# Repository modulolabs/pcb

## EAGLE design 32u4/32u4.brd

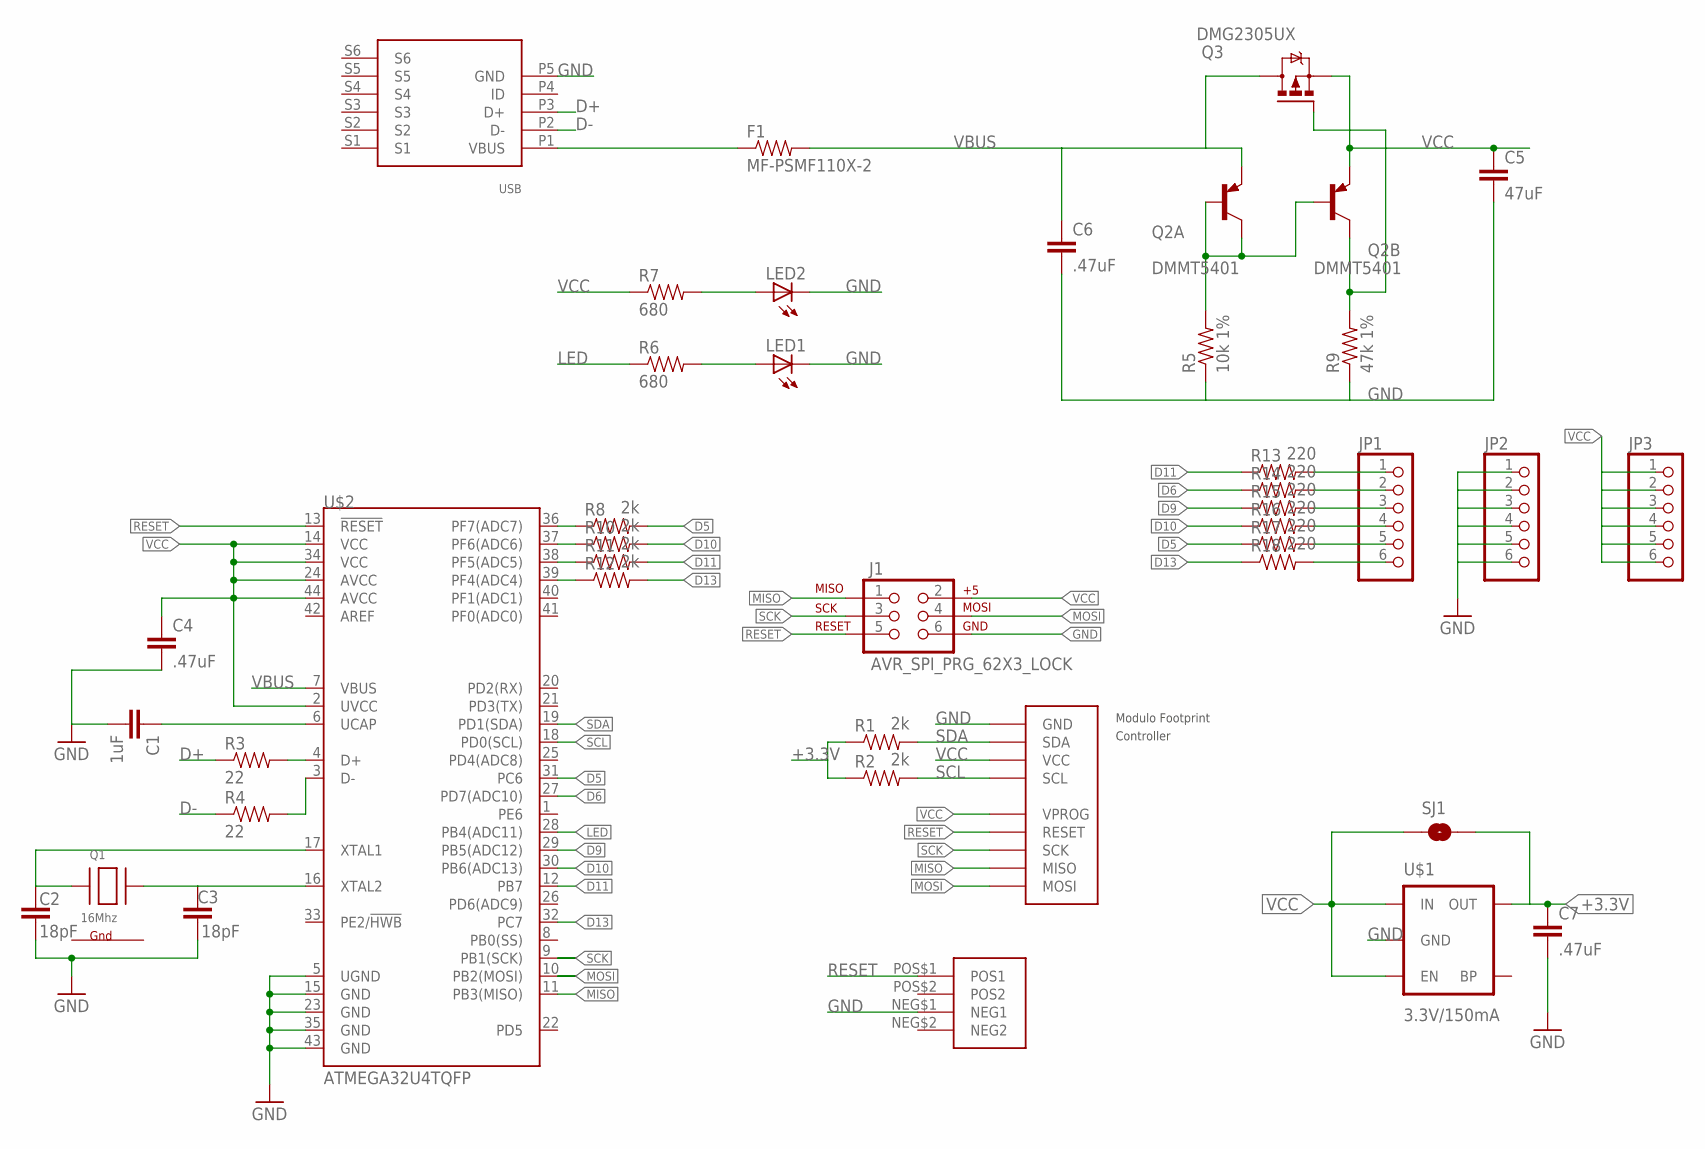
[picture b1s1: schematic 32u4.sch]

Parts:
C1: 1uF; 0805
C2, C3: 18pF; 0805
C4, C6, C7: .47uF; 0805
C5: 47uF; 0805
F1: MF-PSMF110X-2; 0805
FOOTPRINT: Controller; FOOTPRINT2
J1: AVR_SPI_PRG_62X3_LOCK; 2X3_LOCK
JP1, JP2, JP3: PINHD-1X6LOCK; 1X06-BIGLOCK
LED1, LED2: LEDCHIP-LED0805; CHIP-LED0805
Q1: 16Mhz; NX3225
Q2: DMMT5401; SOT-26
Q3: DMG2305UX; MICRO3
R1, R2, R8, R10, R11, R12: 2k; 0805
R3, R4: 22; 0805
R5: 10k 1%; 0805
R6, R7: 680; 0805
R9: 47k 1%; 0805
R13, R14, R15, R16, R17, R18: 220; 0805
SJ1: SOLDERJUMPERNO; SJ_2S-NO
U$1: 3.3V/150mA; SOT23-5
U$2: ATMEGA32U4TQFP; SPARKFUN-DIGITALIC_TQFP44
U$4: USBFCI-MICROB; USB-MICROB-FCI
U$6: TACT-SWITCHBOURNS-7914J; BOURNS-7914J

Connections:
+3.3V: C7.1, R1.1, R2.1, SJ1.2, U$1.5 (OUT)
D0: R12.2, R18.1, U$2.32 (PC7)
D1: R8.2, R17.1, U$2.31 (PC6)
D2: R10.2, R16.1, U$2.30 (PB6(ADC13))
D3: R15.1, U$2.29 (PB5(ADC12))
D4: R14.1, U$2.27 (PD7(ADC10))
D5: R11.2, R13.1, U$2.12 (PB7)
D+: R3.1, U$4.P3 (D+)
D-: R4.1, U$4.P2 (D-)
G1: Q1.4 (G1)
G2: Q1.2 (G2)
GND: C1.2, C2.2, C3.2, C4.2, C5.2, C6.2, C7.2, FOOTPRINT.BUS0 (GND), J1.6, JP2.1, JP2.2, JP2.3, JP2.4, JP2.5, JP2.6, LED1.C, LED2.C, R5.1, R9.1, U$1.2 (GND), U$2.5 (UGND), U$2.15 (GND), U$2.23 (GND), U$2.35 (GND), U$2.43 (GND), U$4.P5 (GND), U$6.NEG$1 (NEG1)
LED: R6.1, U$2.28 (PB4(ADC11))
MISO: FOOTPRINT.PROG3 (MISO), J1.1, U$2.11 (PB3(MISO))
MOSI: FOOTPRINT.PROG4 (MOSI), J1.4, U$2.10 (PB2(MOSI))
unnamed: C1.1, U$2.6 (UCAP)
unnamed: JP1.1, R13.2
unnamed: F1.1, U$4.P1 (VBUS)
unnamed: C3.1, Q1.3 (X2), U$2.16 (XTAL2)
unnamed: LED1.A, R6.2
unnamed: R12.1, U$2.39 (PF4(ADC4))
unnamed: R11.1, U$2.38 (PF5(ADC5))
unnamed: R3.2, U$2.4 (D+)
unnamed: R4.2, U$2.3 (D-)
unnamed: R10.1, U$2.37 (PF6(ADC6))
unnamed: R8.1, U$2.36 (PF7(ADC7))
unnamed: LED2.A, R7.2
unnamed: JP1.2, R14.2
unnamed: Q2.1 (C), Q2.2 (B), Q2.3 (B), R5.2
unnamed: C2.1, Q1.1 (X1), U$2.17 (XTAL1)
unnamed: Q2.4 (C), Q3.1 (G), R9.2
unnamed: JP1.3, R15.2
unnamed: JP1.4, R16.2
unnamed: JP1.5, R17.2
unnamed: JP1.6, R18.2
RESET: FOOTPRINT.PROG1 (RESET), J1.5, U$2.13 (!RESET), U$6.POS$1 (POS1)
SCK: FOOTPRINT.PROG2 (SCK), J1.3, U$2.9 (PB1(SCK))
SCL: FOOTPRINT.BUS3 (SCL), R2.2, U$2.18 (PD0(SCL))
SDA: FOOTPRINT.BUS1 (SDA), R1.2, U$2.19 (PD1(SDA))
VBUS: C6.1, F1.2, Q2.6 (E), Q3.3 (D), U$2.7 (VBUS)
VCC: C4.1, C5.1, FOOTPRINT.BUS2 (VCC), FOOTPRINT.PROG0 (VPROG), J1.2, JP3.1, JP3.2, JP3.3, JP3.4, JP3.5, JP3.6, Q2.5 (E), Q3.2 (S), R7.1, SJ1.1, U$1.1 (IN), U$1.3 (EN), U$2.2 (UVCC), U$2.14 (VCC), U$2.24 (AVCC), U$2.34 (VCC), U$2.44 (AVCC)

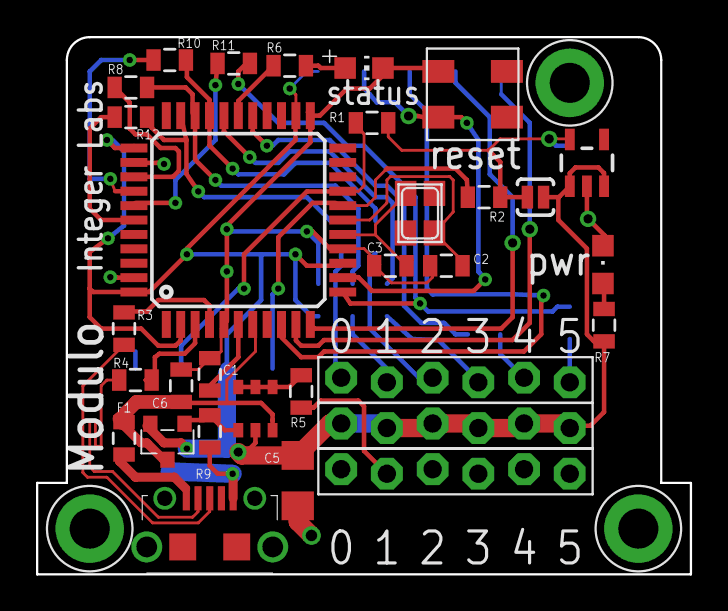
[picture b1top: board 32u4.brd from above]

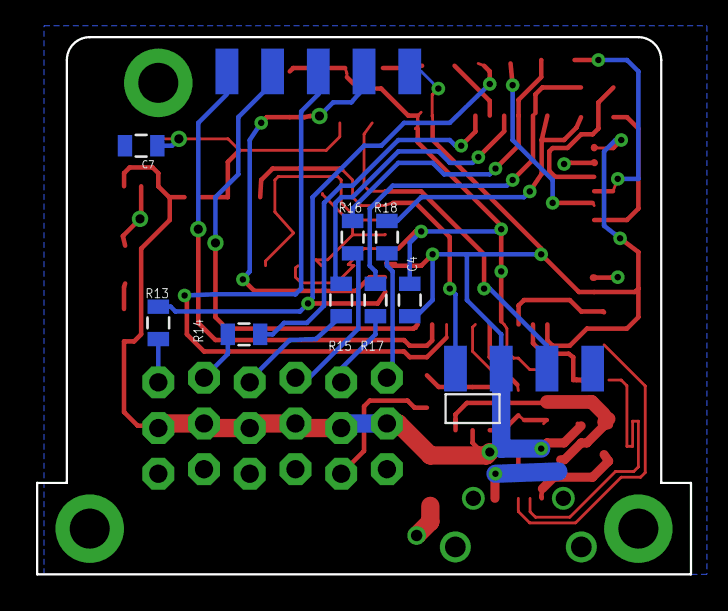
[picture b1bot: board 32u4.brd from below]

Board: 2 copper layers, 36.3 x 29.8 mm, 40 parts (8 on the bottom side), 39 nets.

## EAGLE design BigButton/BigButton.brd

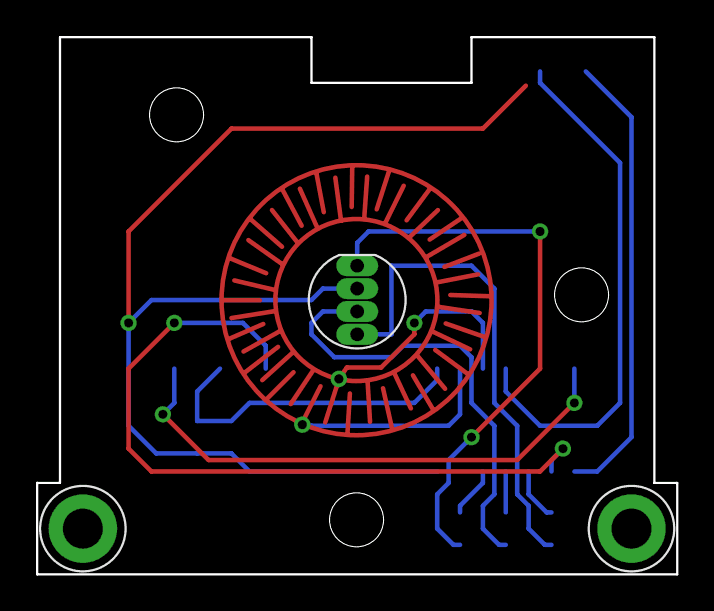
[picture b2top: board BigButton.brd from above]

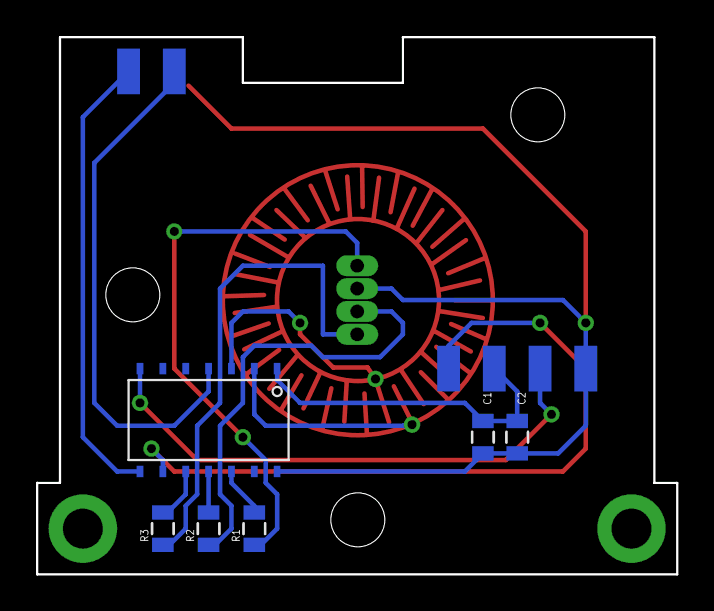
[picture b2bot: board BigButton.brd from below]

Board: 2 copper layers, 35.6 x 29.8 mm, 9 parts (6 on the bottom side), 14 nets.

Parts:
C1: 10uF; 0805
C2: .1uF; 0805
D1: LED-RGB-CC-THRUCLEAR; LED-RGB-THRU
R1, R2, R3: 0805
U$1: BUTTONPAD
U$3: TINY841; SOIC14
U$4: FOOTPRINTFOOTPRINT-2; FOOTPRINT2

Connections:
1: U$1.SIG7, U$3.2
2: U$1.SIG8, U$3.3
B: D1.4, R3.1
G: D1.3, R2.1
GND: C1.1, C2.1, D1.2, U$3.14, U$4.GND
MISO: U$3.8, U$4.MISO
unnamed: R1.2, U$3.12
unnamed: R2.2, U$3.11
unnamed: R3.2, U$3.10
R: D1.1, R1.1
RESET: U$3.4, U$4.RESET
SCL/SCK: U$3.9, U$4.SCL
SDA/MOSI: U$3.7, U$4.SDA
VCC: C1.2, C2.2, U$3.1, U$4.VCC

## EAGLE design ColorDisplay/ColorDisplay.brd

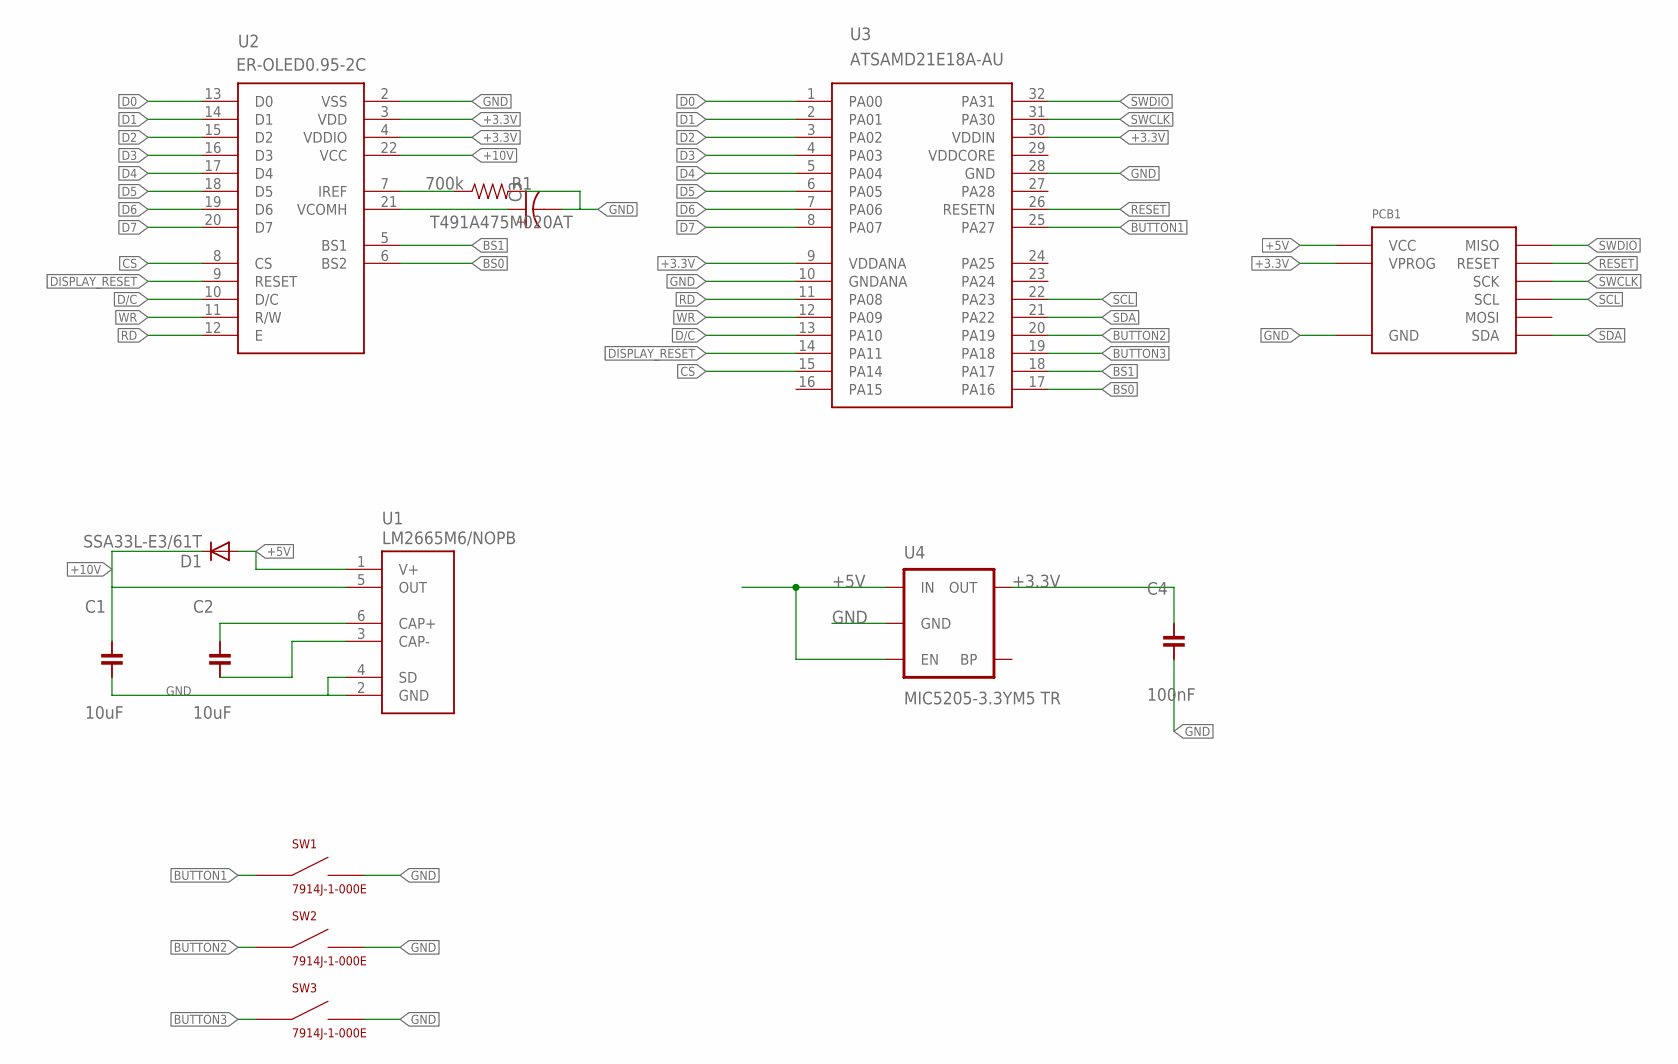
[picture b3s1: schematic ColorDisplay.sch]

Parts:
C1, C2: 10uF; C1206
C3: T491A475M020AT; EIA3216
C4: 100nF; 0603
D1: SSA33L-E3/61T; SMA-DIODE; PARTNUM SSA33L-E3/61T
PCB1: DEVICE-PCB-TABS
R1: 700k; 0603
SW1, SW2, SW3: 7914J-1-000E; BOURNS-7914J
U1: LM2665M6/NOPB; SOT-26
U2: ER-OLED0.95-2C; FPC-24-REVERSE
U3: ATSAMD21E18A-AU; TQFP-32
U4: MIC5205-3.3YM5 TR; SOT23-5

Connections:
+3.3V: C4.1, PCB1.PROG0 (VPROG), U2.3 (VDD), U2.4 (VDDIO), U3.9 (VDDANA), U3.30 (VDDIN), U4.5 (OUT)
+5V: D1.A, PCB1.BUS2 (VCC), U1.1 (V+), U4.1 (IN), U4.3 (EN)
+10V: C1.1, D1.C, U1.5 (OUT), U2.22 (VCC)
BS0: U2.6 (BS2), U3.17 (PA16)
BS1: U2.5 (BS1), U3.18 (PA17)
BUTTON1: SW1.POS$1 (POS1), SW1.POS$2 (POS1), U3.25 (PA27)
BUTTON2: SW2.POS$1 (POS1), SW2.POS$2 (POS1), U3.20 (PA19)
BUTTON3: SW3.POS$1 (POS1), SW3.POS$2 (POS1), U3.19 (PA18)
CS: U2.8 (CS), U3.15 (PA14)
D0: U2.13 (D0), U3.1 (PA00)
D1: U2.14 (D1), U3.2 (PA01)
D2: U2.15 (D2), U3.3 (PA02)
D3: U2.16 (D3), U3.4 (PA03)
D4: U2.17 (D4), U3.5 (PA04)
D5: U2.18 (D5), U3.6 (PA05)
D6: U2.19 (D6), U3.7 (PA06)
D7: U2.20 (D7), U3.8 (PA07)
D/C: U2.10 (D/C), U3.13 (PA10)
DISPLAY_RESET: U2.9 (RESET), U3.14 (PA11)
GND: C1.2, C3.C (-), C4.2, PCB1.BUS0 (GND), R1.2, SW1.NEG$1 (NEG1), SW1.NEG$2 (NEG1), SW2.NEG$1 (NEG1), SW2.NEG$2 (NEG1), SW3.NEG$1 (NEG1), SW3.NEG$2 (NEG1), U1.2 (GND), U1.4 (SD), U2.2 (VSS), U3.10 (GNDANA), U3.28 (GND), U4.2 (GND)
unnamed: C3.A (+), U2.21 (VCOMH)
unnamed: R1.1, U2.7 (IREF)
unnamed: C2.1, U1.6 (CAP+)
unnamed: C2.2, U1.3 (CAP-)
RD: U2.12 (E), U3.11 (PA08)
RESET: PCB1.PROG1 (RESET), U3.26 (RESETN)
SCL: PCB1.BUS3 (SCL), U3.22 (PA23)
SDA: PCB1.BUS1 (SDA), U3.21 (PA22)
SWCLK: PCB1.PROG2 (SCK), U3.31 (PA30)
SWDIO: PCB1.PROG3 (MISO), U3.32 (PA31)
WR: U2.11 (R/W), U3.12 (PA09)

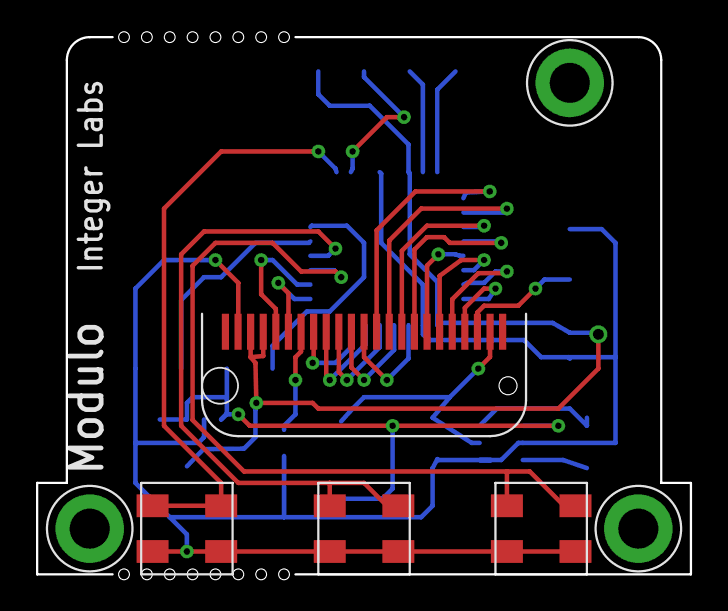
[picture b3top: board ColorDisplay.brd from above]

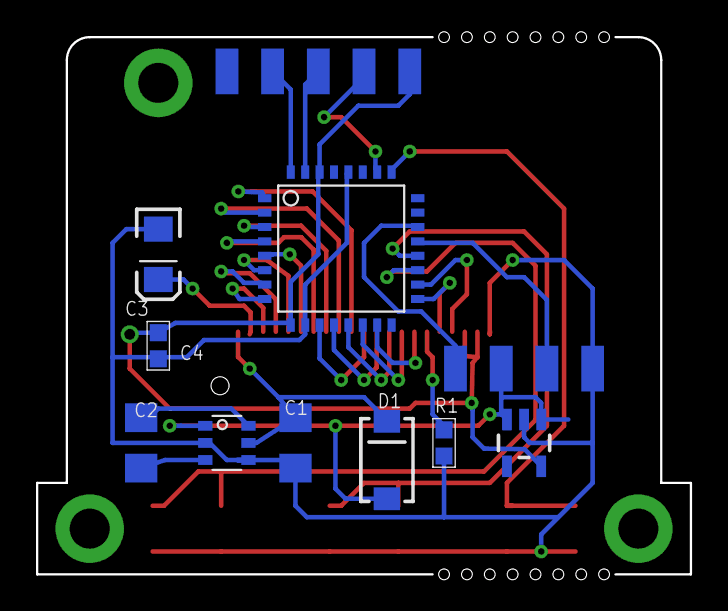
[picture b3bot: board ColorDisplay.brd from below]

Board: 2 copper layers, 14 parts (9 on the bottom side), 31 nets.

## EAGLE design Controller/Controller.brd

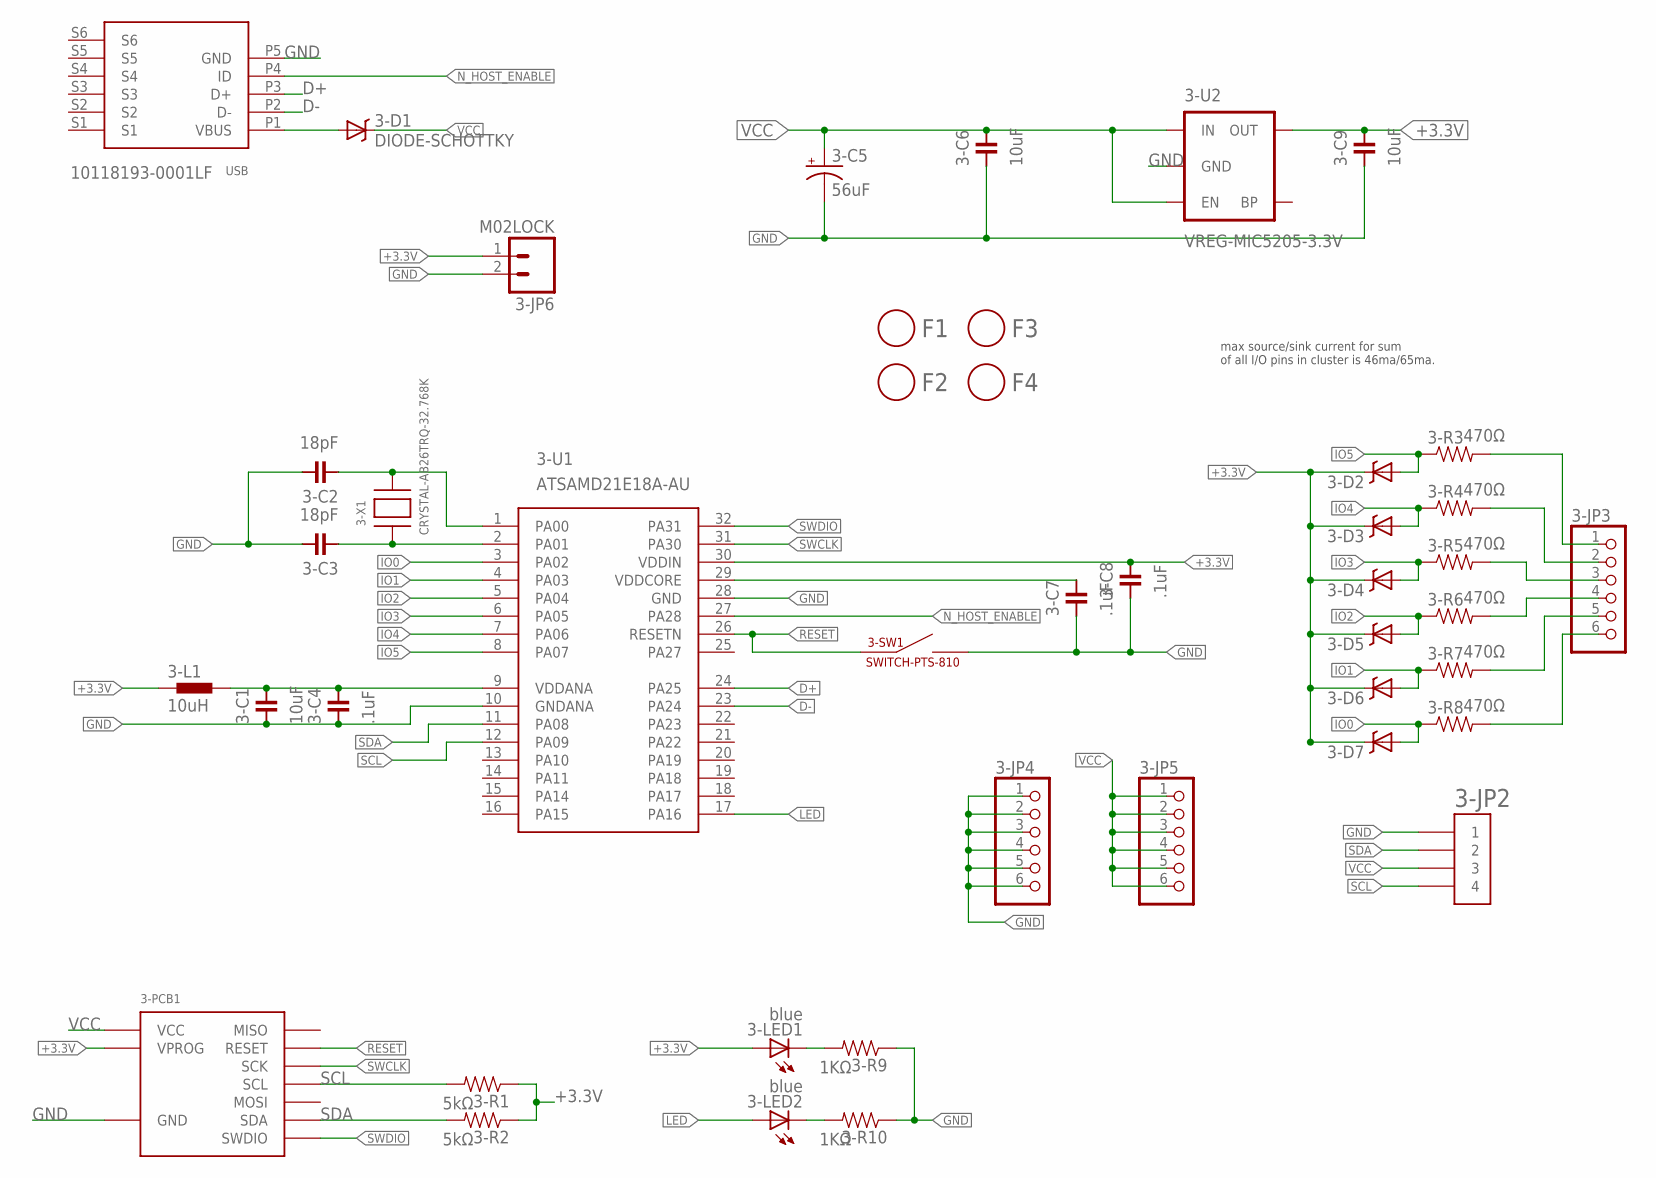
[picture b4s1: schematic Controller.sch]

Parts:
3-C1, 3-C6, 3-C9: 10uF; 0603
3-C2, 3-C3: 18pF; 0603
3-C4, 3-C7, 3-C8: .1uF; 0603
3-C5: 56uF; PANASONIC_D
3-D1: DIODE-SCHOTTKY; SMP
3-D2, 3-D3, 3-D4, 3-D5, 3-D6, 3-D7: DIODE-SCHOTTKY-BAT60A; SOD-323; PARTNUM RB751V40
3-JP1: USBFCI-MICROB; USB-MICROB-FCI; PARTNUM 10118193-0001LF
3-JP2: HEADER-1X4-AMPMODU; AMPMODU-4P
3-JP3, 3-JP4, 3-JP5: PINHD-1X6LOCK; 1X06-BIGLOCK; PARTNUM M20-9990646
3-JP6: M02LOCK; 1X02_LOCK; PARTNUM M20-9990246
3-L1: 10uH; 0603; PARTNUM BLM18TG102TN1D
3-LED1: blue; 0805-LED; PARTNUM LTST-C171KRKT
3-LED2: blue; 0805-LED
3-PCB1: DEVICE-PCB; PARTNUM Controller PCB
3-R1, 3-R2: 5kΩ; 0603
3-R3, 3-R4, 3-R5, 3-R6, 3-R7, 3-R8: 470Ω; 0603
3-R9, 3-R10: 1KΩ; 0603
3-SW1: SWITCH-PTS-810; TACT-SWITCH-PTS-810
3-U1: ATSAMD21E18A-AU; TQFP-32; PARTNUM ATSAMD21E18A-AUT
3-U2: VREG-MIC5205-3.3V; SOT23-5; PARTNUM MIC5205-3.3YM5 TR
3-X1: CRYSTAL-AB26TRQ-32.768K; CRYSTAL-AB26TRQ
F1, F2, F3, F4: FIDUCIAL; FIDUCIAL_1MM

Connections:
+3.3V: 3-C8.1, 3-C9.1, 3-D2.C, 3-D3.C, 3-D4.C, 3-D5.C, 3-D6.C, 3-D7.C, 3-JP6.1, 3-L1.1, 3-LED1.A, 3-PCB1.VPROG, 3-R1.1, 3-R2.1, 3-U1.30 (VDDIN), 3-U2.5 (OUT)
D+: 3-JP1.P3 (D+), 3-U1.24 (PA25)
D-: 3-JP1.P2 (D-), 3-U1.23 (PA24)
GND: 3-C1.2, 3-C2.1, 3-C3.1, 3-C4.2, 3-C5.-, 3-C6.2, 3-C7.2, 3-C8.2, 3-C9.2, 3-JP1.P5 (GND), 3-JP2.P$1 (1), 3-JP2.P$2 (1), 3-JP4.1, 3-JP4.2, 3-JP4.3, 3-JP4.4, 3-JP4.5, 3-JP4.6, 3-JP6.2, 3-PCB1.GND, 3-R9.1, 3-R10.1, 3-SW1.P$3 (NEG1), 3-SW1.P$4 (NEG1), 3-U1.10 (GNDANA), 3-U1.28 (GND), 3-U2.2 (GND)
IO0: 3-D7.A, 3-R8.1, 3-U1.3 (PA02)
IO1: 3-D6.A, 3-R7.1, 3-U1.4 (PA03)
IO2: 3-D5.A, 3-R6.1, 3-U1.5 (PA04)
IO3: 3-D4.A, 3-R5.1, 3-U1.6 (PA05)
IO4: 3-D3.A, 3-R4.1, 3-U1.7 (PA06)
IO5: 3-D2.A, 3-R3.1, 3-U1.8 (PA07)
LED: 3-LED2.A, 3-U1.17 (PA16)
unnamed: 3-LED1.C, 3-R9.2
unnamed: 3-JP3.1, 3-R3.2
unnamed: 3-D1.A, 3-JP1.P1 (VBUS)
unnamed: 3-LED2.C, 3-R10.2
unnamed: 3-C2.2, 3-U1.1 (PA00), 3-X1.XOUT (X2)
unnamed: 3-C3.2, 3-U1.2 (PA01), 3-X1.XIN (X1)
unnamed: 3-JP3.2, 3-R4.2
unnamed: 3-JP3.3, 3-R5.2
unnamed: 3-JP3.4, 3-R6.2
unnamed: 3-JP3.5, 3-R7.2
unnamed: 3-JP3.6, 3-R8.2
unnamed: 3-C1.1, 3-C4.1, 3-L1.2, 3-U1.9 (VDDANA)
unnamed: 3-C7.1, 3-U1.29 (VDDCORE)
N_HOST_ENABLE: 3-JP1.P4 (ID), 3-U1.27 (PA28)
RESET: 3-PCB1.RESET, 3-SW1.P$1 (POS1), 3-SW1.P$2 (POS1), 3-U1.26 (RESETN)
SCL: 3-JP2.P$7 (4), 3-JP2.P$8 (4), 3-PCB1.SCL, 3-R1.2, 3-U1.12 (PA09)
SDA: 3-JP2.P$3 (2), 3-JP2.P$4 (2), 3-PCB1.SDA, 3-R2.2, 3-U1.11 (PA08)
SWCLK: 3-PCB1.CLK (SCK), 3-U1.31 (PA30)
SWDIO: 3-PCB1.SWDIO, 3-U1.32 (PA31)
VCC: 3-C5.+, 3-C6.1, 3-D1.C, 3-JP2.P$5 (3), 3-JP2.P$6 (3), 3-JP5.1, 3-JP5.2, 3-JP5.3, 3-JP5.4, 3-JP5.5, 3-JP5.6, 3-PCB1.VCC, 3-U2.1 (IN), 3-U2.3 (EN)

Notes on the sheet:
max source/sink current for sum of all I/O pins in cluster is 46ma/65ma.

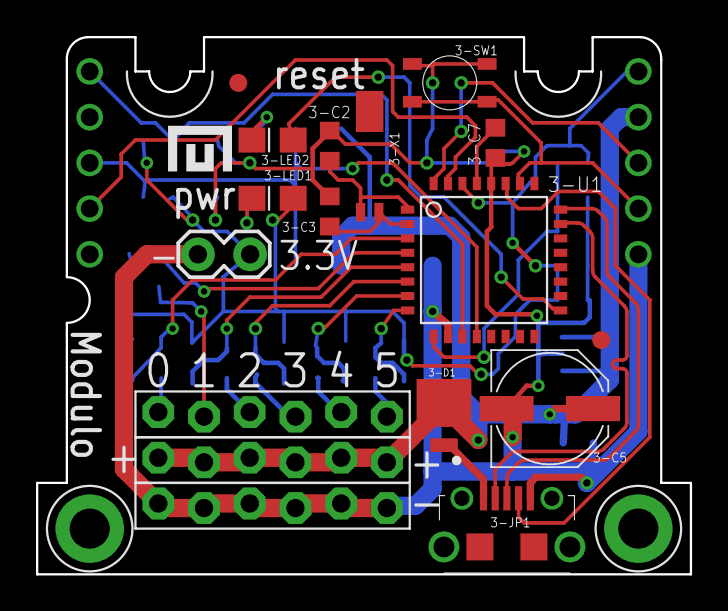
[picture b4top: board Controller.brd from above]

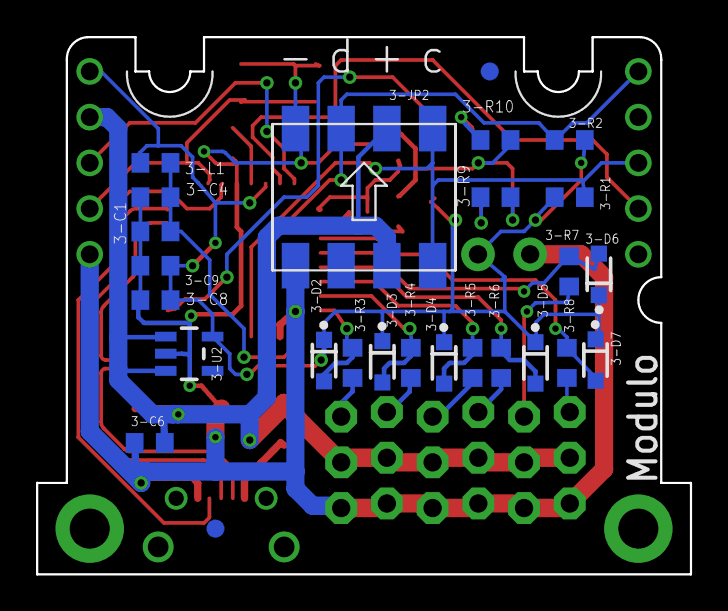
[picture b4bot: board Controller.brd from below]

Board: 2 copper layers, 36.3 x 29.8 mm, 45 parts (26 on the bottom side), 31 nets.

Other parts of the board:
U$2: LOGO-TINY

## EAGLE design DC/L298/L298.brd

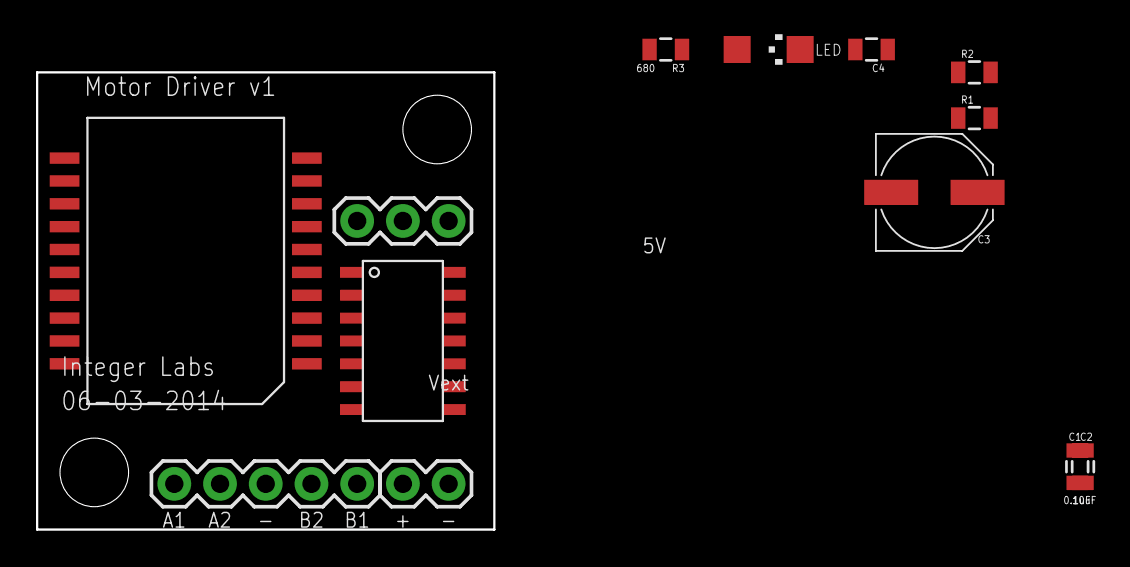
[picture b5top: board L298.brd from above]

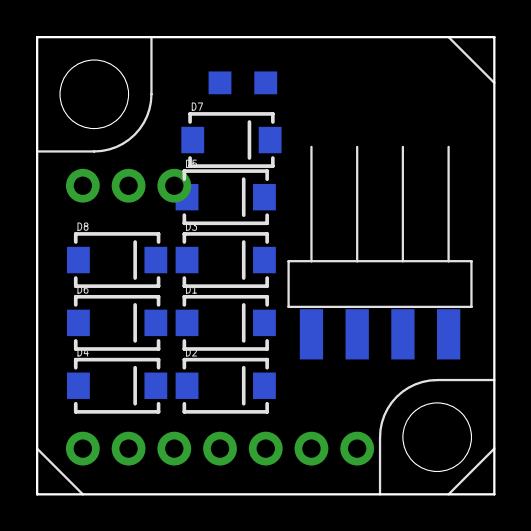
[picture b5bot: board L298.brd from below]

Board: 2 copper layers, 25.4 x 25.4 mm, 22 parts (8 on the bottom side), 21 nets, no tracks yet.

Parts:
C1, C4: 0.1uF; 0805
C2: 10uF; 0805
C3: 10uF; PANASONIC_D
D1, D2, D3, D4, D5, D6, D7, D8: DIODE-SCHOTTKY_; SMA-DIODE
JP1: 1X05
JP2: M02PTH; 1X02
JP3: 1X03
LED: blue; CHIPLED_1206
R1, R2: 0805
R3: 680; 0805
U$3: TINY841; SOIC14
U$4: FOOTPRINT
U$6: L298_BRIDGE_DRIVER; POWERSO20

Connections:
ENA: U$3.2, U$6.8
ENB: U$3.3, U$6.14
GND: C1.1, C2.1, C3.-, C4.2, D1.A, D3.A, D5.A, D7.A, JP1.3, JP2.1, LED.C, R1.1, R2.2, U$3.14, U$4.P$3, U$6.1, U$6.10, U$6.11, U$6.20
IN1: U$3.13, U$6.7
IN2: U$3.12, U$6.9
IN3: U$3.11, U$6.13
IN4: U$3.10, U$6.15
MISO/LED: U$3.8, U$4.MISO
unnamed: LED.A, R3.1
OUT1: D1.C, D2.A, JP1.5, U$6.4
OUT2: D3.C, D4.A, JP1.4, U$6.5
OUT3: D5.C, D6.A, JP1.1, U$6.16
OUT4: D7.C, D8.A, JP1.2, U$6.17
RESET: U$3.4, U$4.RESET
SCL/SCK: U$3.9, U$4.P$4
SDA/MOSI: U$3.7, U$4.P$2
SENSEA: R1.2, U$3.5, U$6.2
SENSEB: R2.1, U$3.6, U$6.19
VCC: C1.2, C2.2, JP3.3, U$3.1, U$4.P$1, U$6.12
VIN: JP2.2, JP3.1
VM: C3.+, C4.1, D2.C, D4.C, D6.C, D8.C, JP3.2, U$6.6

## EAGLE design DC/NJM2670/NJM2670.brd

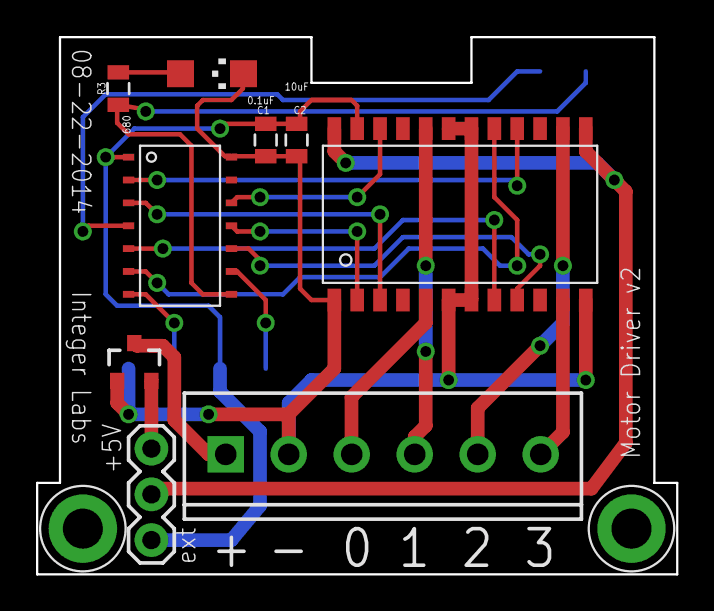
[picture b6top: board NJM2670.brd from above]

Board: 2 copper layers, 35.6 x 29.8 mm, 10 parts (0 on the bottom side), 21 nets.

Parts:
C1: 0.1uF; 0805
C2: 10uF; 0805
JP3: 1X03
JP4: SCREWTERMINAL-3.5MM-6
LED: blue; CHIPLED_1206
Q1: MOSFET-PCHANNELIRLML2244; SOT23-3
R3: 680; 0805
U$3: TINY841; SOIC14
U$4: FOOTPRINTFOOTPRINT-2; FOOTPRINT2
U$6: NJM2670; SOP-24-E3

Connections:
ENABLEA: U$3.3, U$6.3
ENABLEB: U$3.10, U$6.9
GND: C1.1, C2.1, JP4.2, LED.C, Q1.1, U$3.14, U$4.GND, U$6.1, U$6.6, U$6.7, U$6.12, U$6.18, U$6.19
INA1: U$3.11, U$6.2
INA2: U$3.12, U$6.22
INB1: U$3.5, U$6.8
INB2: U$3.6, U$6.17
MISO/LED: R3.2, U$3.8, U$4.MISO
unnamed: JP3.3, Q1.2
unnamed: LED.A, R3.1
unnamed: JP4.3, U$6.5
unnamed: JP4.4, U$6.20
unnamed: JP4.5, U$6.14
unnamed: JP4.6, U$6.11
RESET: U$3.4, U$4.RESET
SCL/SCK: U$3.9, U$4.SCL
SDA/MOSI: U$3.7, U$4.SDA
TSD: U$3.2, U$6.16
VCC: C1.2, C2.2, JP3.1, U$3.1, U$4.VCC, U$6.23
VIN: JP4.1, Q1.3
VS: JP3.2, U$6.13, U$6.24

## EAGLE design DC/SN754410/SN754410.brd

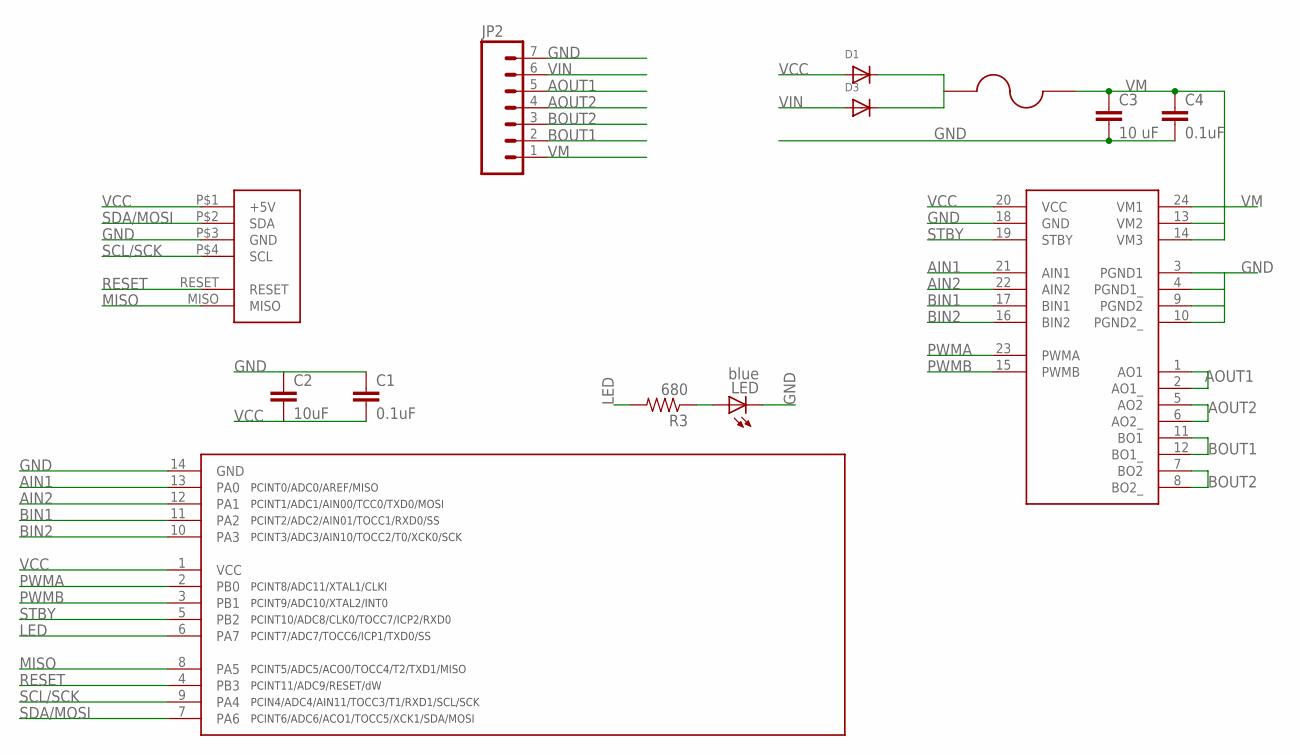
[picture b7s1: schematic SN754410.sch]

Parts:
C1, C4: 0.1uF; 0805
C2: 10uF; 0805
C3: 10 uF; 0805
D1, D3: DIODESOD-123; SOD-123
JP2: M07; 1X07
LED: blue; CHIPLED_1206
R3: 680; 0805
U$1: TB6612FNG; SSOP-24
U$2: FUSE; 1812
U$3: TINY841; SOIC14
U$4: FOOTPRINT

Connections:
AIN1: U$1.21 (AIN1), U$3.13 (PA0)
AIN2: U$1.22 (AIN2), U$3.12 (PA1)
AOUT1: JP2.5, U$1.1 (AO1), U$1.2 (AO1_)
AOUT2: JP2.4, U$1.5 (AO2), U$1.6 (AO2_)
BIN1: U$1.17 (BIN1), U$3.11 (PA2)
BIN2: U$1.16 (BIN2), U$3.10 (PA3)
BOUT1: JP2.2, U$1.11 (BO1), U$1.12 (BO1_)
BOUT2: JP2.3, U$1.7 (BO2), U$1.8 (BO2_)
GND: C1.1, C2.1, C3.2, C4.2, JP2.7, LED.C, U$1.3 (PGND1), U$1.4 (PGND1_), U$1.9 (PGND2), U$1.10 (PGND2_), U$1.18 (GND), U$3.14 (GND), U$4.P$3 (GND)
LED: R3.2, U$3.6 (PA7)
MISO: U$3.8 (PA5), U$4.MISO
unnamed: D1.C, D3.C, U$2.P$1 (1)
unnamed: LED.A, R3.1
PWMA: U$1.23 (PWMA), U$3.2 (PB0)
PWMB: U$1.15 (PWMB), U$3.3 (PB1)
RESET: U$3.4 (PB3), U$4.RESET
SCL/SCK: U$3.9 (PA4), U$4.P$4 (SCL)
SDA/MOSI: U$3.7 (PA6), U$4.P$2 (SDA)
STBY: U$1.19 (STBY), U$3.5 (PB2)
VCC: C1.2, C2.2, D1.A, U$1.20 (VCC), U$3.1 (VCC), U$4.P$1 (+5V)
VIN: D3.A, JP2.6
VM: C3.1, C4.1, JP2.1, U$1.13 (VM2), U$1.14 (VM3), U$1.24 (VM1), U$2.P$2 (2)

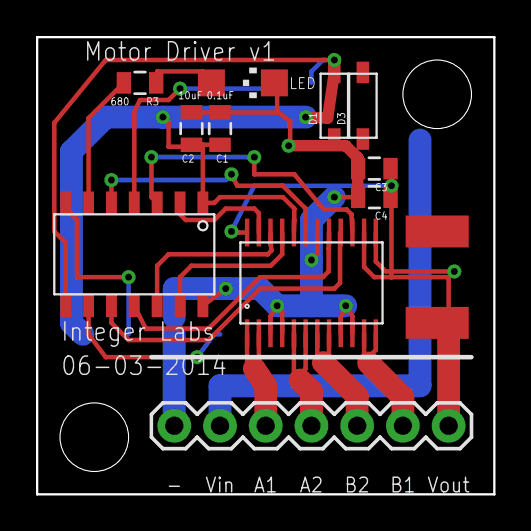
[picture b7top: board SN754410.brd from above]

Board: 2 copper layers, 25.4 x 25.4 mm, 13 parts (0 on the bottom side), 22 nets.

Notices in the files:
parts and their libraries:
SparkFun-DigitalIC: Licensing: Creative Commons ShareAlike 4.0 International - https://creativecommons.org/licenses/by-sa/4.0
